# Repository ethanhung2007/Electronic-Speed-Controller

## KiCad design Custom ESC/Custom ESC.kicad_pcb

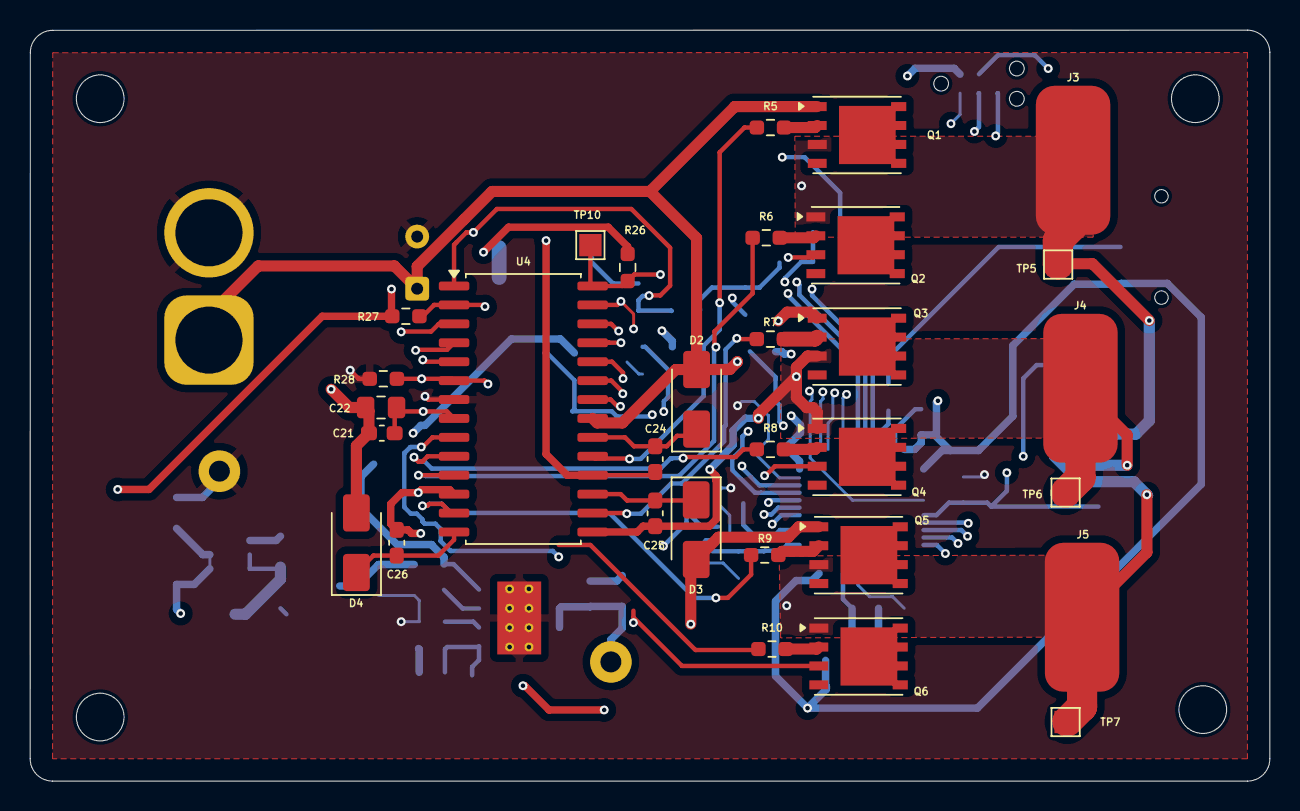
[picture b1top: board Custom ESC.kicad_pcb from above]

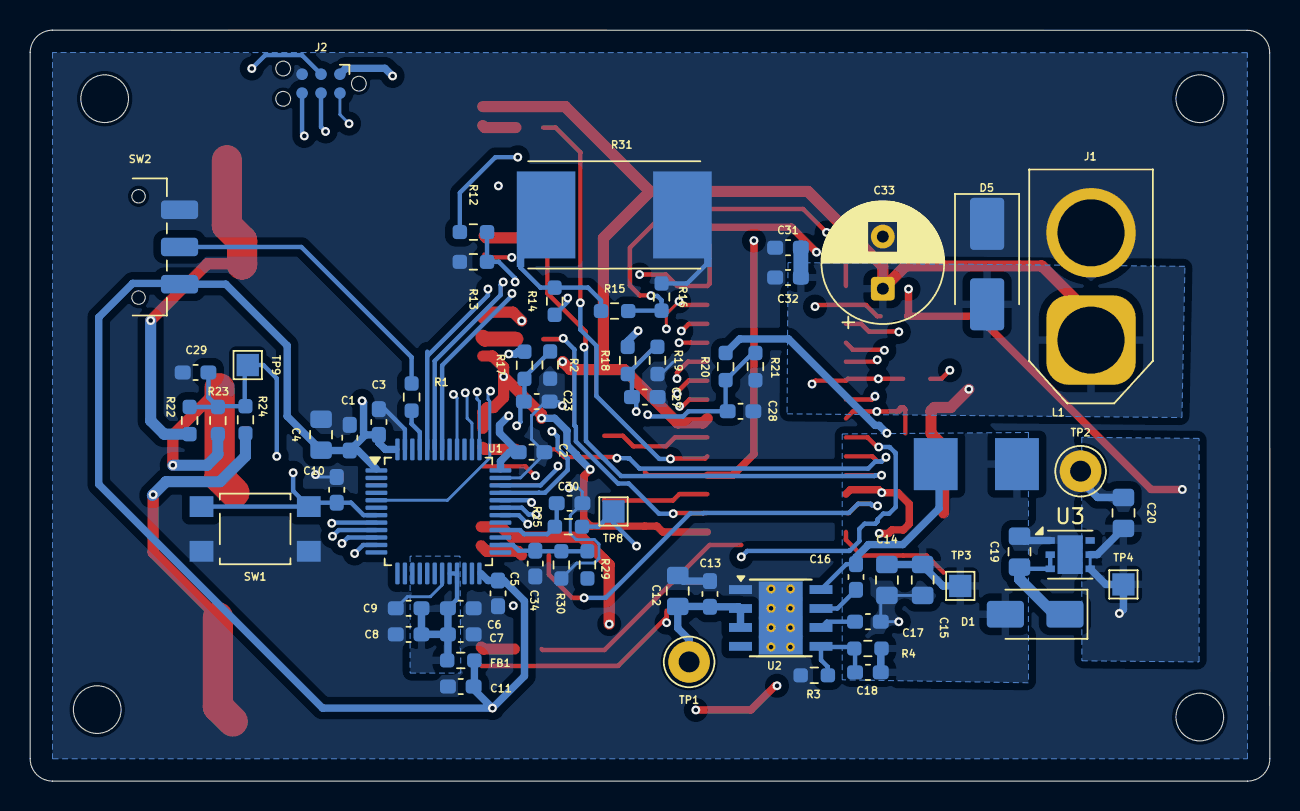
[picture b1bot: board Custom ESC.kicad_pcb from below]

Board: 4 copper layers, 83.2 x 50.4 mm, 102 parts (67 on the bottom side), 54 nets.

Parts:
 : MountingHole_3.2mm_M3
 #2,  #3,  #4: MountingHole_3.2mm_M3
C1, C2, C3, C5, C8, C10, C16, C21, C32, C34: 0.1u; C_0603_1608Metric_Pad1.08x0.95mm_HandSolder
C4, C12, C19, C20, C22: 4.7u; C_0805_2012Metric_Pad1.18x1.45mm_HandSolder
C6: 10n; C_0603_1608Metric_Pad1.08x0.95mm_HandSolder
C7, C9, C11, C17, C24, C25, C26, C31: 1u; C_0603_1608Metric_Pad1.08x0.95mm_HandSolder
C13: 220n; C_0603_1608Metric_Pad1.08x0.95mm_HandSolder
C14, C15: 22u; C_0805_2012Metric_Pad1.18x1.45mm_HandSolder
C18: 100p; C_0603_1608Metric_Pad1.08x0.95mm_HandSolder
C23, C27, C28, C29, C30: 1n; C_0603_1608Metric_Pad1.08x0.95mm_HandSolder
C33: 220u; CP_Radial_D8.0mm_P3.50mm
D1: 40V; D_SMA
D2, D3, D4: SS14; D_SMA
D5: SMBJ15A-E3/52; D_SMB_Handsoldering
FB1: 600; R_0603_1608Metric_Pad0.98x0.95mm_HandSolder
J1: XT60-F; AMASS_XT60-F_1x02_P7.20mm_Vertical
J2: Conn_ARM_SWD_TagConnect_TC2030-NL; Tag-Connect_TC2030-IDC-NL_2x03_P1.27mm_Vertical
J3: MOTOR_A; SolderWirePad_1x01_SMD_5x10mm
J4: MOTOR_B; SolderWirePad_1x01_SMD_5x10mm
J5: MOTOR_C; SolderWirePad_1x01_SMD_5x10mm
L1: 10u; Inductor_SMD_Wurth_WE-LHMI_8.4x6.6mm
Q1, Q2, Q3, Q4, Q5, Q6: NMOS; PowerPAK_SO-8_Single
R1, R2, R12, R13, R14, R15, R16, R19, R21, R26, R27, R28: 10k; R_0603_1608Metric_Pad0.98x0.95mm_HandSolder
R3: 24.9k; R_0603_1608Metric_Pad0.98x0.95mm_HandSolder
R4, R29: 100k; R_0603_1608Metric_Pad0.98x0.95mm_HandSolder
R5, R6, R7, R8, R9, R10: 25.5; R_0603_1608Metric_Pad0.98x0.95mm_HandSolder
R17, R18, R20, R22, R23, R24: 33k; R_0603_1608Metric_Pad0.98x0.95mm_HandSolder
R25: 100; R_0603_1608Metric_Pad0.98x0.95mm_HandSolder
R30: 27k; R_0603_1608Metric_Pad0.98x0.95mm_HandSolder
R31: 2m; R_Shunt_Vishay_WSR2_WSR3_KelvinConnection
SW1: SW_Push; SW_SPST_TL3305B
SW2: SW_SPDT; SW_SPDT_CK_JS102011SAQN
TP1: VCC; TestPoint_Loop_D2.60mm_Drill1.4mm_Beaded
TP2: GND; TestPoint_Loop_D2.60mm_Drill1.4mm_Beaded
TP3: +5V; TestPoint_Pad_1.5x1.5mm
TP4: +3V3; TestPoint_Pad_1.5x1.5mm
TP5: VS1; TestPoint_Pad_1.5x1.5mm
TP6: VS2; TestPoint_Pad_1.5x1.5mm
TP7: VS3; TestPoint_Pad_1.5x1.5mm
TP8: CAO; TestPoint_Pad_1.5x1.5mm
TP9: VNEUT; TestPoint_Pad_1.5x1.5mm
TP10: FAULT; TestPoint_Pad_1.5x1.5mm
U1: STM32G4A1CETx; LQFP-48_7x7mm_P0.5mm
U2: LMR33610ADDAR; Texas_HSOP-8-1EP_3.9x4.9mm_P1.27mm_ThermalVias
U3: LDO40LPU33RY; DFN-6-1EP_3x3mm_P0.95mm_EP1.7x2.6mm
U4: IR2133S; SOIC-28W_7.5x17.9mm_P1.27mm

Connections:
+3V3: C1.1, C2.1, C3.1, C4.1, C5.1, C11.1, C20.1, FB1.2, J2.1 (VCC), R26.2, R27.2, SW2.3 (C), TP4.1, U1.1 (VBAT), U1.24 (VDD), U1.36 (VDD), U1.48 (VDD), U3.4 (Vout), U3.5 (Vsense)
+3V3A: C6.1, C7.1, C8.1, C9.1, FB1.1, U1.20 (VREF+), U1.21 (VDDA)
+5V: C14.1, C15.1, C18.1, D1.2 (A), L1.2, R4.2, TP3.1
/BEMF_A: C23.1, R2.2, R17.1, U1.8 (PA0)
/BEMF_B: C27.1, R18.1, R19.2, U1.9 (PA1)
/BEMF_C: C28.1, R20.1, R21.2, U1.10 (PA2)
/BOOT0: R1.2, U1.45 (PB8)
/CA+: R14.1, U4.5 (CA+)
/CA-: R12.1, R13.2, U4.4 (CA-)
/CAO: R12.2, R25.1, TP8.1, U4.3 (CAO)
/COM: C21.2, C22.2, Q2.3 (S), Q4.3 (S), Q6.3 (S), R14.2, R15.2, R31.1, U4.8 (COM)
/CUR_SENSE: C30.1, R25.2, U1.28 (PB14)
/FAULT: R26.1, TP10.1, U1.42 (PB5), U4.28 (~FAULT)
/FLT-CLR: R27.1, U1.43 (PB6), U4.2 (~FLT-CLR)
/HIN1: U1.30 (PA8), U4.22 (~HIN1)
/HIN2: U1.31 (PA9), U4.23 (~HIN2)
/HIN3: U1.32 (PA10), U4.24 (~HIN3)
/HO1: R5.1, U4.19 (HO1)
/HO2: R7.1, U4.16 (HO2)
/HO3: R9.1, U4.13 (HO3)
/ITRIP: R15.1, R16.2, U4.1 (ITRIP)
/LIN1: U1.33 (PA11), U4.25 (~LIN1)
/LIN2: U1.34 (PA12), U4.26 (~LIN2)
/LIN3: U1.5 (PF0), U4.27 (~LIN3)
/LO1: R6.1, U4.11 (LO1)
/LO2: R8.1, U4.10 (LO2)
/LO3: R10.1, U4.9 (LO3)
/NRST: C10.1, J2.3 (~RESET), SW1.2, U1.7 (PG10)
/SD: R28.1, U1.44 (PB7), U4.6 (SD)
/SWCLK: J2.4 (SWCLK), U1.38 (PA14)
/SWDIO: J2.2 (SWDIO), U1.37 (PA13)
/SWO: J2.6 (SWO), U1.40 (PB3)
/SW_BOOT0: R1.1, SW2.2 (B)
/VB1: C24.1, D2.1 (K), U4.20 (VB1)
/VB2: C25.1, D3.1 (K), U4.17 (VB2)
/VB3: C26.1, D4.1 (K), U4.14 (VB3)
/VBAT_SENSE: C34.2, R29.1, R30.2, U1.26 (PB12)
/VNEUT: C29.1, R22.1, R23.1, R24.1, TP9.1, U1.11 (PA3)
/VS1: C24.2, J3.1, Q1.3 (S), Q2.1 (D), R17.2, R22.2, TP5.1, U4.18 (VS1)
/VS2: C25.2, J4.1, Q3.3 (S), Q4.1 (D), R18.2, R23.2, TP6.1, U4.15 (VS2)
/VS3: C26.2, J5.1, Q5.3 (S), Q6.1 (D), R20.2, R24.2, TP7.1, U4.12 (VS3)
GND: C1.2, C2.2, C3.2, C4.2, C5.2, C6.2, C7.2, C8.2, C9.2, C10.2, C11.2, C12.2, C13.2, C14.2, C15.2, C17.2, C19.2, C20.2, C23.2, C27.2, C28.2, C29.2, C30.2, C31.2, C32.2, C33.2, C34.1, D5.1 (K), J1.2, J2.5 (GND), R2.1, R3.1, R13.1, R16.1, R19.1, R21.1, R28.2, R30.1, R31.2, SW1.1, SW2.1 (A), TP2.1, U1.19 (VSSA), U1.23 (VSS), U1.35 (VSS), U1.47 (VSS), U2.1 (GND), U2.9 (GND), U3.1 (GND), U3.7 (GND), U4.7 (VSS)
unnamed: C19.1, D1.1 (K), U3.2 (EN), U3.3 (Vin)
unnamed: Q1.2 (G), R5.2
unnamed: Q2.2 (G), R6.2
unnamed: Q3.2 (G), R7.2
unnamed: Q4.2 (G), R8.2
unnamed: Q5.2 (G), R9.2
unnamed: Q6.2 (G), R10.2
unnamed: C16.1, U2.7 (BOOT)
unnamed: C18.2, R3.2, R4.1, U2.5 (FB)
unnamed: C16.2, L1.1, U2.8 (SW)
unnamed: C17.1, U2.6 (VCC)
VCC: C12.1, C13.1, C21.1, C22.1, C31.1, C32.1, C33.1, D2.2 (A), D3.2 (A), D4.2 (A), D5.2 (A), J1.1, Q1.1 (D), Q3.1 (D), Q5.1 (D), R29.2, TP1.1, U2.2 (VIN), U2.3 (EN), U4.21 (VCC)

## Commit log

2026-03-06 Initial Add
2026-03-09 Did CurrentSense
    Implemented CurrentSense schematic using the IR2133S gate driver's internal current sense amplifier. Need to implement Back EMF and then layouts!
2026-03-09 Test
2026-03-09 Fixed up some minor schematic details
2026-04-06 DONE!!
2026-04-06 fixed some stuff
2026-04-14 fixed some DRC stuff, still have some issues
2026-04-22 lowkey don't know what i chnaged
